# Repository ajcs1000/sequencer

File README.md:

# 8-Step CD4017 Sequencer

***THIS HAS NOT BEEN FULLY MANUFACTURED OR TESTED. BUILD AT YOUR OWN RISK.***

This is a Eurorack 8-step sequencer made for a class, based off a modification of the Baby 8 sequencer. It uses a CD4017 decade counter, and a 555-based clock. You may want to mess around with the clock speed range if you decide to build it; it's maybe a little small and might not cover what you want it to. Same goes for LED brightness. They were a little bright when I breadboarded it, so test it out before assembling. 

This includes a faceplate design as a PCB file; as with the actual PCB it hasn't been manufactured yet and isn't guaranteed to be perfect. 

This was designed in KiCad 6, and all the needed files *should* be here - please feel free to contact me if I left something out.

Updates to come eventually, hopefully.

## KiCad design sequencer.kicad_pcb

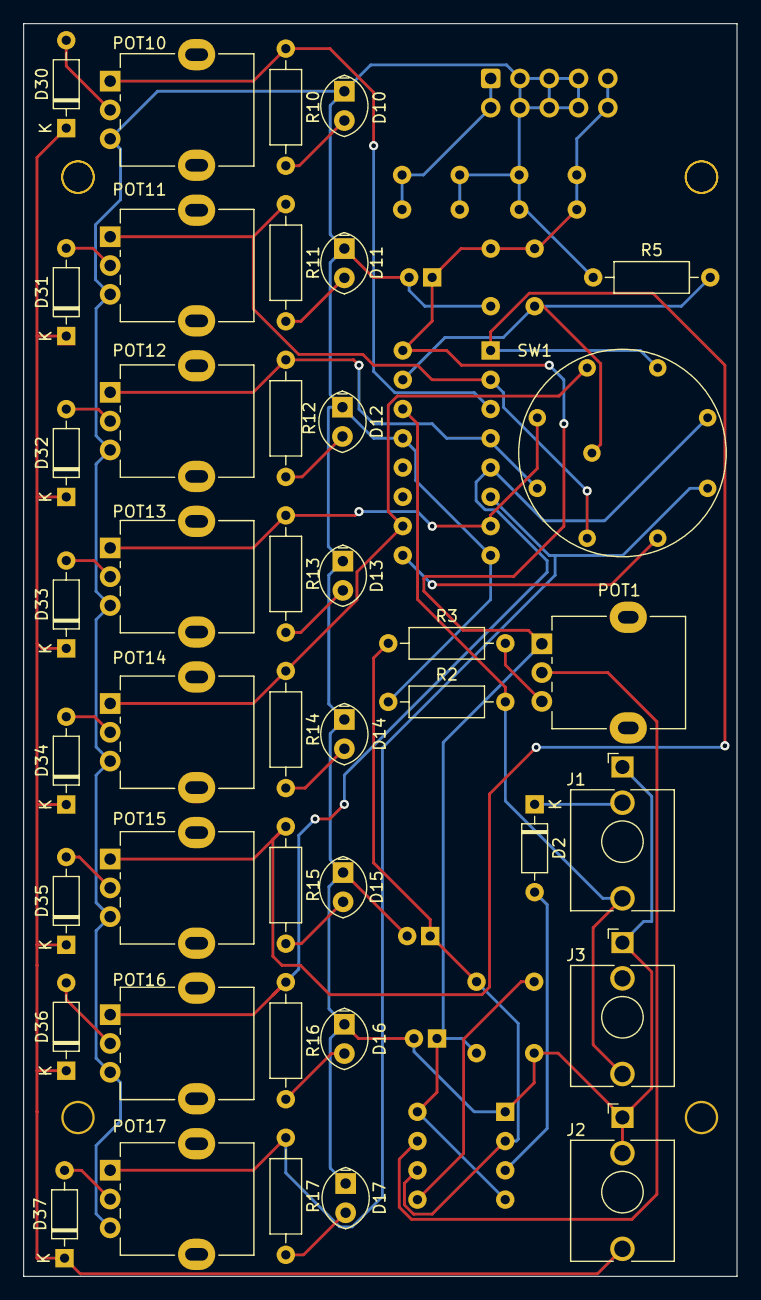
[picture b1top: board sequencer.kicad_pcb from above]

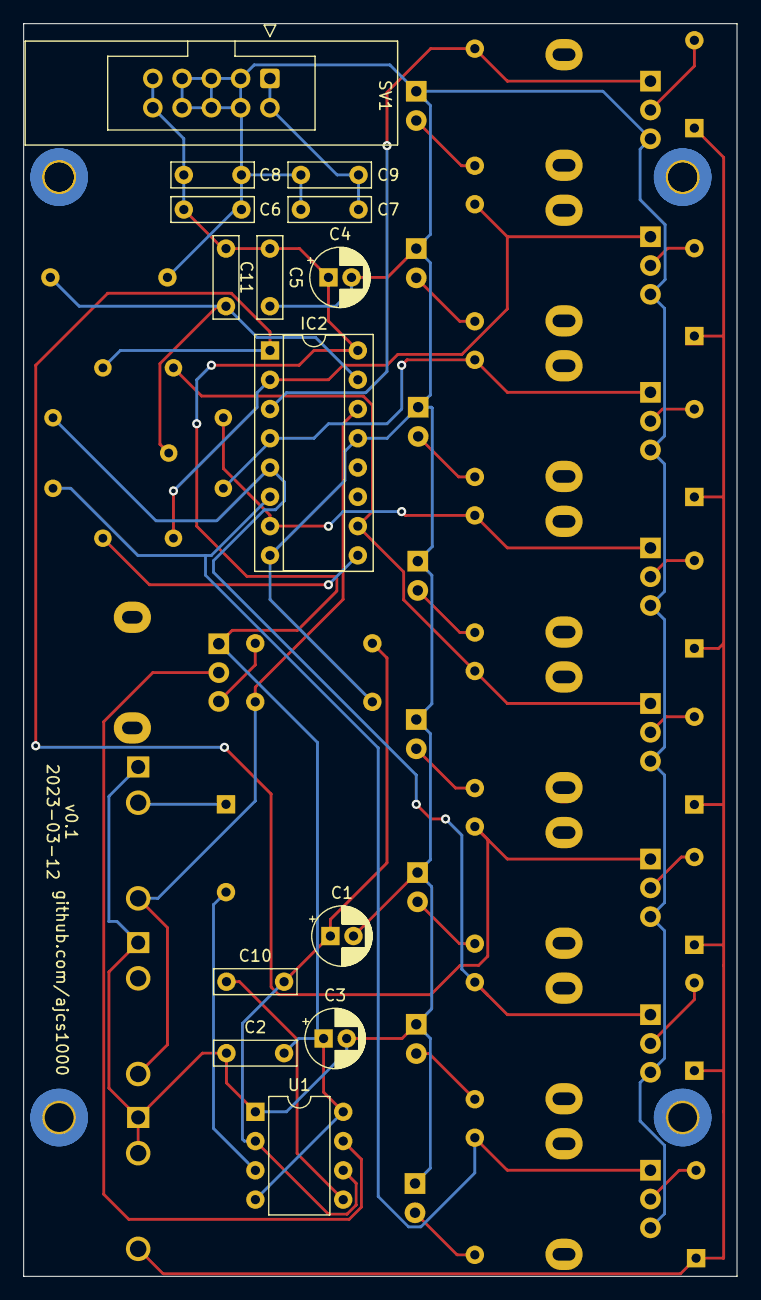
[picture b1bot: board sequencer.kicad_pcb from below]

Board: 2 copper layers, 61.9 x 108.7 mm, 55 parts (14 on the bottom side), 37 nets.

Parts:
C1, C3, C4: 10uF; CP_Radial_D5.0mm_P2.00mm
C2, C5, C6, C7, C8, C9, C10: 10nF; C_Rect_L7.0mm_W2.0mm_P5.00mm
C11: .22uF; C_Rect_L7.0mm_W2.0mm_P5.00mm
D2, D30, D31, D32, D33, D34, D35, D36, D37: D; D_DO-35_SOD27_P7.62mm_Horizontal
D10, D11, D12, D13, D14, D15, D16, D17: LED; LED_Oval_W5.2mm_H3.8mm
IC2: 4017; DIP-16_W7.62mm_Socket
J1, J2, J3: AudioJack2_Ground; Jack_3.5mm_QingPu_WQP-PJ398SM_Vertical_CircularHoles
POT1: 50k; Potentiometer_Alpha_RD901F-40-00D_Single_Vertical
POT10, POT11, POT12, POT13, POT14, POT15, POT16, POT17: 100k; Potentiometer_Alpha_RD901F-40-00D_Single_Vertical2mmholes
R2: 100k; R_Axial_DIN0207_L6.3mm_D2.5mm_P10.16mm_Horizontal
R3: 1k; R_Axial_DIN0207_L6.3mm_D2.5mm_P10.16mm_Horizontal
R5: 47k; R_Axial_DIN0207_L6.3mm_D2.5mm_P10.16mm_Horizontal
R10, R11, R12, R13, R14, R15, R16, R17: 5k; R_Axial_DIN0207_L6.3mm_D2.5mm_P10.16mm_Horizontal
SV1: ML10; IDC-Header_2x05_P2.54mm_Latch_Vertical
SW1: SW_Rotary8; SW_rotary8
U1: NE555P; DIP-8_W7.62mm

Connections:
+15V: C2.2, C3.1, C4.1, C5.1, C6.1, C8.1, C11.1, IC2.16 (VDD), POT1.1, SV1.9, SV1.10, U1.4 (R), U1.8 (VCC)
-15V: C7.2, C9.2, SV1.1, SV1.2
GND: C1.2, C2.1, C3.2, C4.2, C5.2, C6.2, C7.1, C8.2, C9.1, D10.1 (K), D11.1 (K), D12.1 (K), D13.1 (K), D14.1 (K), D15.1 (K), D16.1 (K), D17.1 (K), IC2.8 (VSS), IC2.13 (CKEN), J1.S, J2.S, J2.TN, J3.S, POT10.3, POT11.3, POT12.3, POT13.3, POT14.3, POT15.3, POT16.3, POT17.3, R2.1, R5.1, SV1.3, SV1.4, SV1.5, SV1.6, SV1.7, SV1.8, U1.1 (GND)
unnamed: C1.1, C10.2, R3.1, U1.2 (TR), U1.6 (THR)
unnamed: C10.1, U1.5 (CV)
unnamed: C11.2, IC2.15 (Reset), R5.2, SW1.9
unnamed: D2.1 (K), J1.TN
unnamed: D2.2 (A), U1.3 (OUT)
unnamed: D10.2 (A), R10.2
unnamed: D11.2 (A), R11.2
unnamed: D12.2 (A), R12.2
unnamed: D13.2 (A), R13.2
unnamed: D14.2 (A), R14.2
unnamed: D15.2 (A), R15.2
unnamed: D16.2 (A), R16.2
unnamed: D17.2 (A), R17.2
unnamed: D30.1 (K), D31.1 (K), D32.1 (K), D33.1 (K), D34.1 (K), D35.1 (K), D36.1 (K), D37.1 (K), J2.T
unnamed: D30.2 (A), POT10.2
unnamed: D31.2 (A), POT11.2
unnamed: D32.2 (A), POT12.2
unnamed: D33.2 (A), POT13.2
unnamed: D34.2 (A), POT14.2
unnamed: D35.2 (A), POT15.2
unnamed: D36.2 (A), POT16.2
unnamed: D37.2 (A), POT17.2
unnamed: IC2.1 (Q5), POT15.1, R15.1, SW1.5
unnamed: IC2.2 (Q1), POT11.1, R11.1, SW1.1
unnamed: IC2.3 (Q0), POT10.1, R10.1
unnamed: IC2.4 (Q2), POT12.1, R12.1, SW1.2
unnamed: IC2.5 (Q6), POT16.1, R16.1, SW1.6
unnamed: IC2.6 (Q7), POT17.1, R17.1, SW1.7
unnamed: IC2.7 (Q3), POT13.1, R13.1, SW1.3
unnamed: IC2.9 (Q8), SW1.8
unnamed: IC2.10 (Q4), POT14.1, R14.1, SW1.4
unnamed: IC2.14 (CLK), J1.T, J3.T, R2.2
unnamed: POT1.2, U1.7 (DIS)
unnamed: POT1.3, R3.2
